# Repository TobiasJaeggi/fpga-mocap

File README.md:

# FPGA-based low-cost motion capture
Infrared-based motion capture.
Image processing is done the [GECKO5Modular](https://github.com/logisim-evolution/GECKO5Education) (formerly GECKO5Education V2.0), an educational FPGA platform.
I created this system as part of masters degree in electrical engineering at Bern University of Applied Sciences (BFH).

> [!NOTE]
> Solving marker correspondence using epipolar geometry is not yet implemented.
> As a result, the Python software is currently only able to track a single marker.

# Blob Detector
Marker detection unit hosting FGPA, microcontroller, IR camera, IR LEDs and PoE module.

# Demo
The system tracking a reflective marker.

[demo video](https://youtu.be/6Va6dF9vp88)

# Mechanical design
[onshape project](https://cad.onshape.com/documents/1d5331a2d4403797078fc34d/w/9683c0b739c4abd1173768d9/e/775ed87ad6031a9883c39a66?renderMode=0&uiState=687d36ef6178f96628e9789b)

# Documentation
`doc/Low-Cost_Motion_Capture.pdf`

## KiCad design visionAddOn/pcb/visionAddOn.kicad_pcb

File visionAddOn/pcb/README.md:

# `visionAddOn/hardware`
An addon for the [GECKO5Education](https://github.com/logisim-evolution/GECKO5Education) intended for IR based MoCap featuring
- STM32F767 with external RAM, EEPROM and external Watchdog
- Power Over Ethernet
- Connector for [KLT-E4MPF-OV9281 V4.2 NIR Camera](http://modulecamera.com)
- switchable 5V supply for external IR stroble LED
# known issues
## V1.0
### nINT/REFCLK0 does not output a clock
Pin 2 (LED2/nINIT/nPME/nINTSEL) on LAN87 needs a pulldown. Also, remove pulldown on LED1/nINT/nPME/REGOFF.
 
# Attribution
## Project Template
This project is based on the GECKO5 [addonTemplate](https://github.com/logisim-evolution/GECKO5Education/tree/main/kicad/addonTemplate)

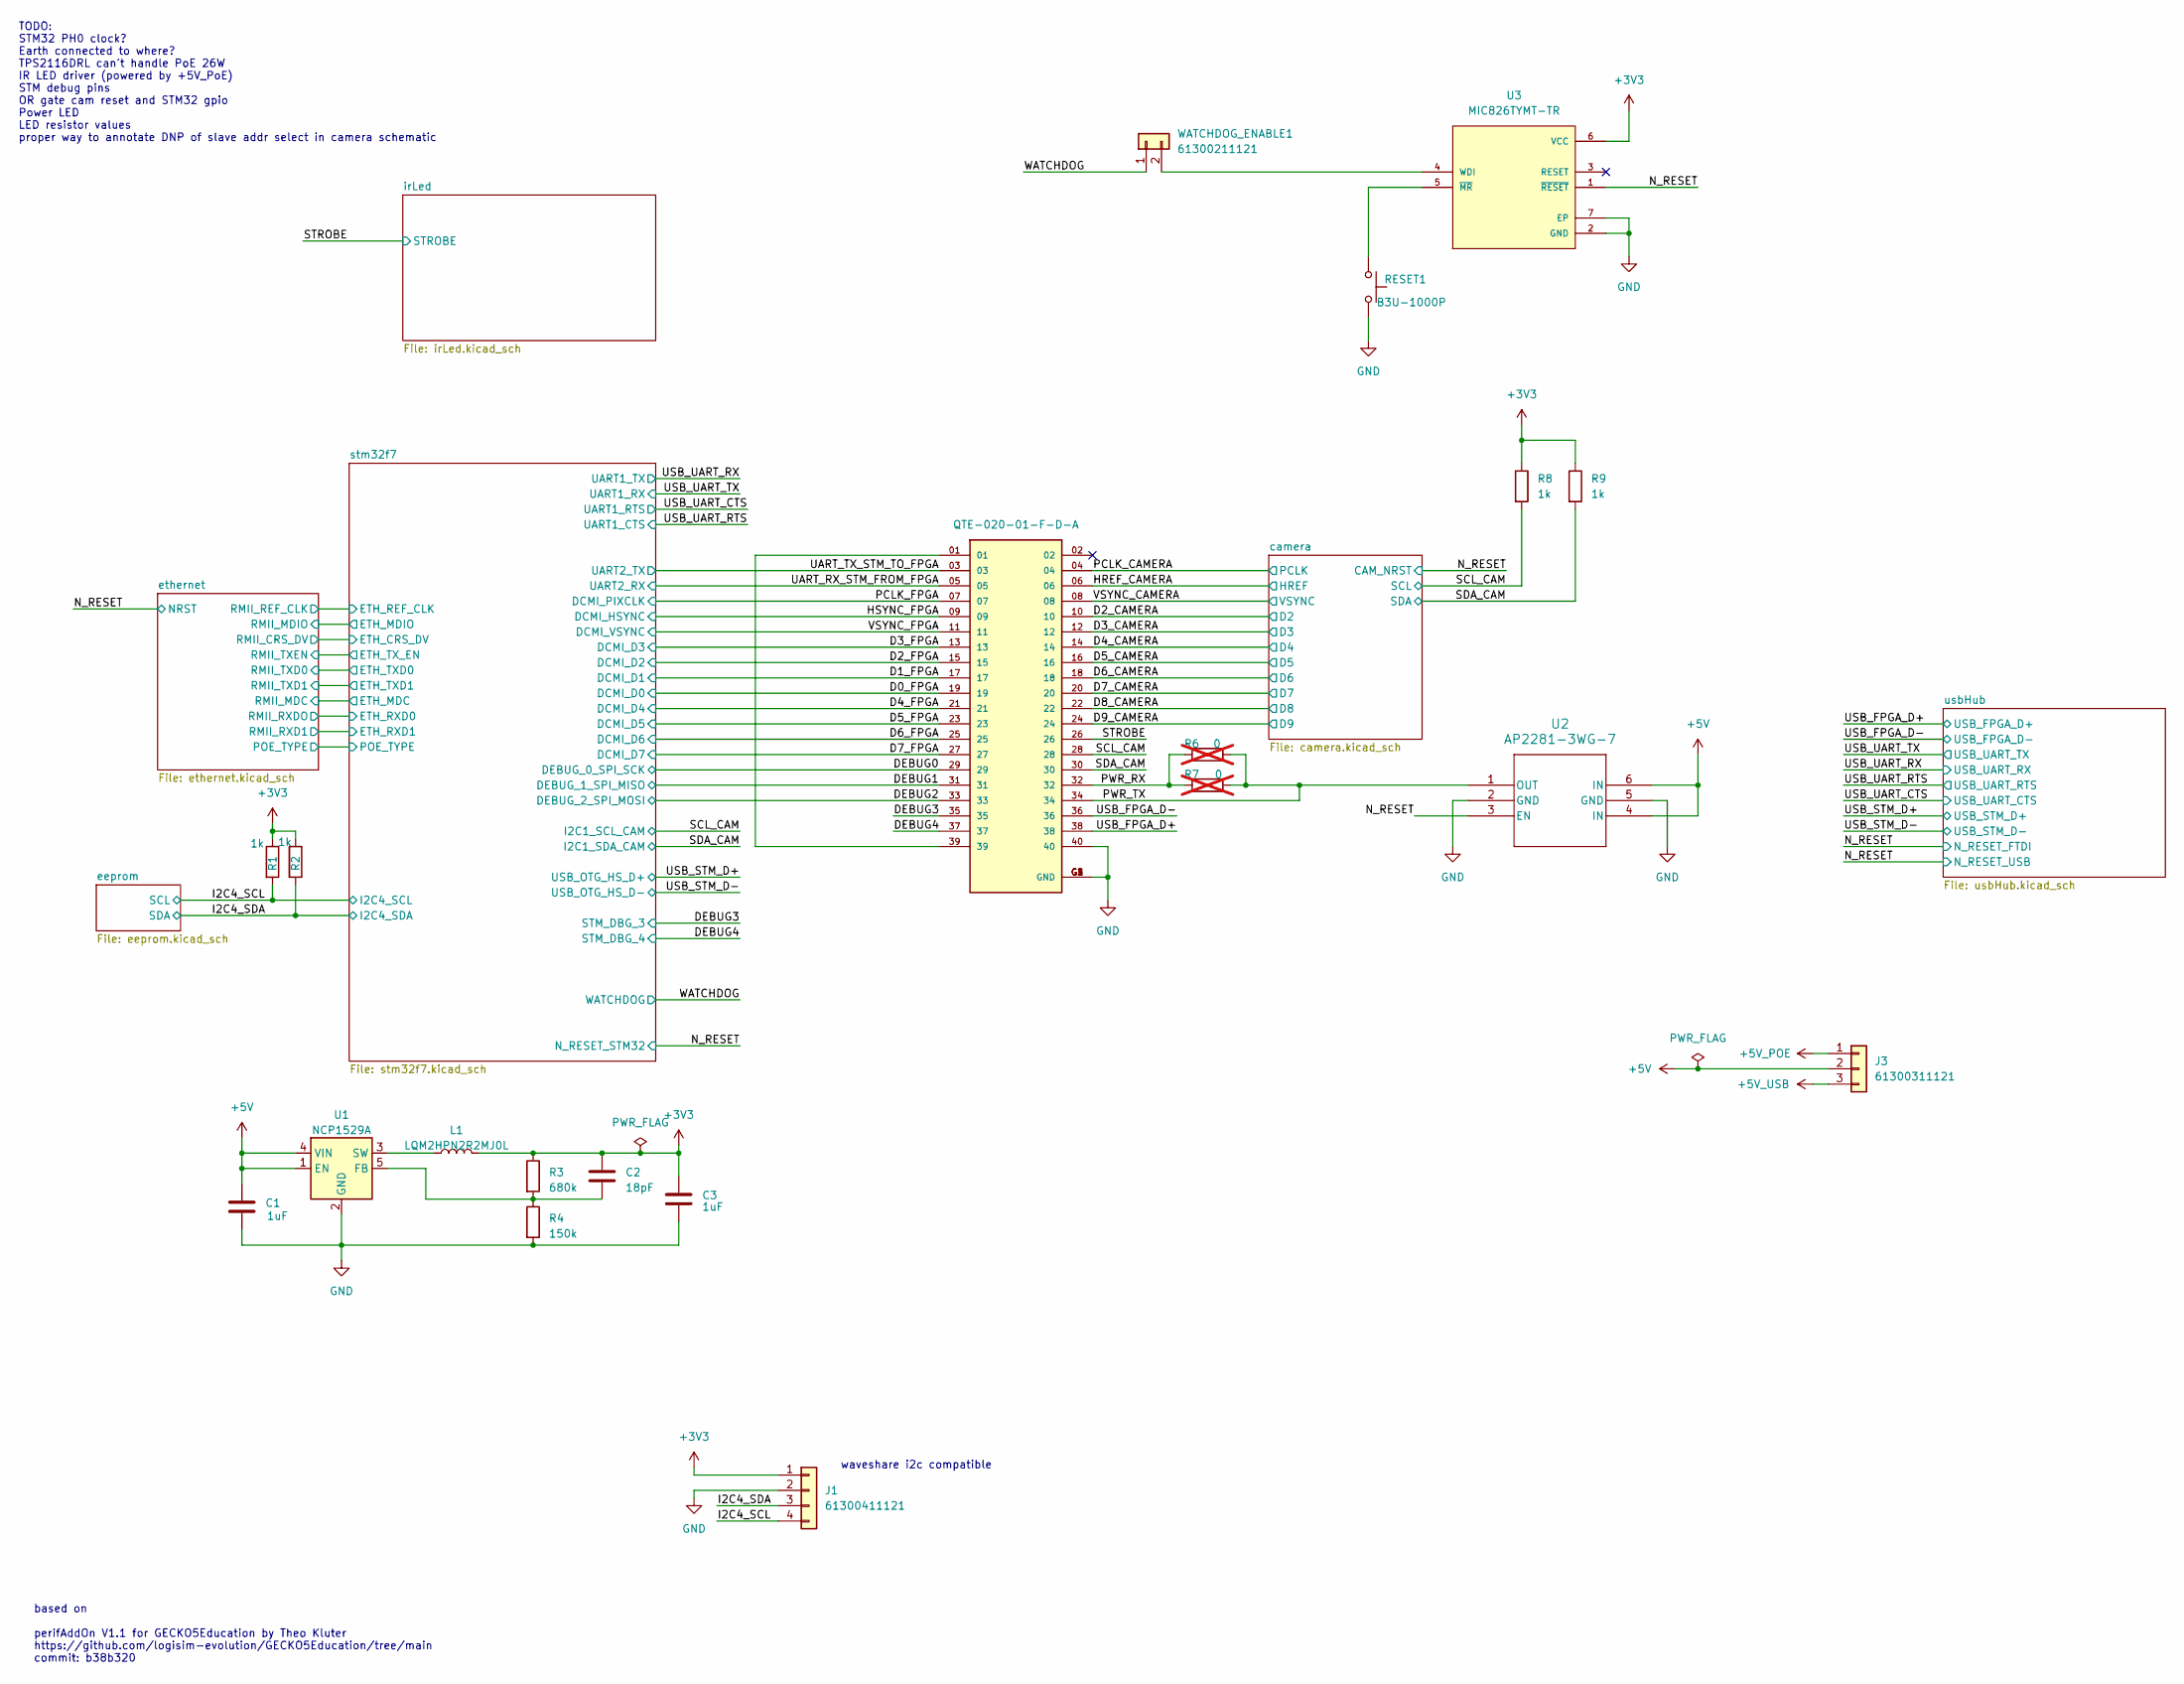
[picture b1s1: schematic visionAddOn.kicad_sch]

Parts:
C1, C3: 1uF; C_0603_1608Metric; DigiKey-Partnumber 445-4112-2-ND
C2: 18pF; C_0402_1005Metric; DigiKey-Partnumber 490-8082-2-ND
J1: 61300411121; PinHeader_1x04_P2.54mm_Vertical; DigiKey-Partnumber 732-5317-ND
J2: QTE-020-01-F-D-A; SAMTEC_QTE-020-01-X-D-A; DigiKey-Partnumber 612-QTE-020-01-F-D-A-TR-ND
J3: 61300311121; PinHeader_1x03_P2.54mm_Vertical; DigiKey-Partnumber 732-5316-ND
L1: LQM2HPN2R2MJ0L; DigiKey-Partnumber 490-6700-2-ND
R1, R2, R8, R9: 1k; R_0402_1005Metric; DigiKey-Partnumber 311-1.0KJRTR-ND
R3: 680k; R_0402_1005Metric; DigiKey-Partnumber 311-680KJRTR-ND
R4: 150k; R_0402_1005Metric; DigiKey-Partnumber 311-150KLRTR-ND
R6, R7: 0; R_0402_1005Metric; DigiKey-Partnumber 311-0.0JRTR-ND; not fitted
RESET1: B3U-1000P; SW_B3U-1000P_OMR; DigiKey-Partnumber SW1020TR-ND
U1: NCP1529A; SOT-23-5; DigiKey-Partnumber NCP1529ASNT1GOSTR-ND
U2: AP2281-3WG-7; SOT26_DIO; DigiKey-Partnumber AP2281-3WG-7DITR-ND
U3: MIC826TYMT-TR; MIC826TYMT-TR_SON50P160X160X60-7N; DigiKey-Partnumber 576-4375-2-ND
WATCHDOG_ENABLE1: 61300211121; PinHeader_1x02_P2.54mm_Vertical; DigiKey-Partnumber 732-5315-ND

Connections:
+3V3: C2.1, C3.1, J1.1, L1.2, R1.1, R2.1, R3.1, R8.1, R9.1, U3.6 (VCC); also elsewhere on the board
+5V: C1.1, J3.2, U1.1 (EN), U1.4 (VIN), U2.4 (IN), U2.6 (IN)
+5V_POE: J3.1; also elsewhere on the board
+5V_USB: J3.3; also elsewhere on the board
/D0_FPGA: J2.19; also elsewhere on the board
/D1_FPGA: J2.17; also elsewhere on the board
/D2_CAMERA: J2.10; also elsewhere on the board
/D2_FPGA: J2.15; also elsewhere on the board
/D3_CAMERA: J2.12; also elsewhere on the board
/D3_FPGA: J2.13; also elsewhere on the board
/D4_CAMERA: J2.14; also elsewhere on the board
/D4_FPGA: J2.21; also elsewhere on the board
/D5_CAMERA: J2.16; also elsewhere on the board
/D5_FPGA: J2.23; also elsewhere on the board
/D6_CAMERA: J2.18; also elsewhere on the board
/D6_FPGA: J2.25; also elsewhere on the board
/D7_CAMERA: J2.20; also elsewhere on the board
/D7_FPGA: J2.27; also elsewhere on the board
/D8_CAMERA: J2.22; also elsewhere on the board
/D9_CAMERA: J2.24; also elsewhere on the board
/DEBUG0: J2.29; also elsewhere on the board
/DEBUG1: J2.31; also elsewhere on the board
/DEBUG2: J2.33; also elsewhere on the board
/DEBUG3: J2.35; also elsewhere on the board
/DEBUG4: J2.37; also elsewhere on the board
/HREF_CAMERA: J2.06; also elsewhere on the board
/HSYNC_FPGA: J2.09; also elsewhere on the board
/I2C4_SCL: J1.4, R1.2; also elsewhere on the board
/I2C4_SDA: J1.3, R2.2; also elsewhere on the board
/N_RESET: U2.3 (EN), U3.1 (~RESET); also elsewhere on the board
/PCLK_CAMERA: J2.04; also elsewhere on the board
/PCLK_FPGA: J2.07; also elsewhere on the board
/PWR_RX: J2.32, R6.1, R7.1
/PWR_TX: J2.34, R6.2, R7.2, U2.1 (OUT)
/SCL_CAM: J2.28, R8.2; also elsewhere on the board
/SDA_CAM: J2.30, R9.2; also elsewhere on the board
/STROBE: J2.26; also elsewhere on the board
/UART_RX_STM_FROM_FPGA: J2.05; also elsewhere on the board
/UART_TX_STM_TO_FPGA: J2.03; also elsewhere on the board
/USB_FPGA_D+: J2.38; also elsewhere on the board
/USB_FPGA_D-: J2.36; also elsewhere on the board
/VSYNC_CAMERA: J2.08; also elsewhere on the board
/VSYNC_FPGA: J2.11; also elsewhere on the board
/WATCHDOG: WATCHDOG_ENABLE1.1; also elsewhere on the board
GND: C1.2, C3.2, J1.2, J2.40, J2.G1 (GND), J2.G2 (GND), J2.G3 (GND), J2.G4 (GND), R4.2, RESET1.2, U1.2 (GND), U2.2 (GND), U2.5 (GND), U3.2 (GND), U3.7 (EP); also elsewhere on the board
unnamed: J2.01, J2.39
unnamed: C2.2, R3.2, R4.1, U1.5 (FB)
unnamed: L1.1, U1.3 (SW)
unnamed: U3.4 (WDI), WATCHDOG_ENABLE1.2
unnamed: RESET1.1, U3.5 (~MR)

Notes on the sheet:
waveshare i2c compatible
TODO: STM32 PH0 clock? Earth connected to where? TPS2116DRL can't handle PoE 26W IR LED driver (powered by +5V_PoE) STM debug pins OR gate cam reset and STM32 gpio Power LED LED resistor values proper way to annotate DNP of slave addr select in camera schematic
based on perifAddOn V1.1 for GECKO5Education by Theo Kluter https://github.com/logisim-evolution/GECKO5Education/tree/main commit: b38b320

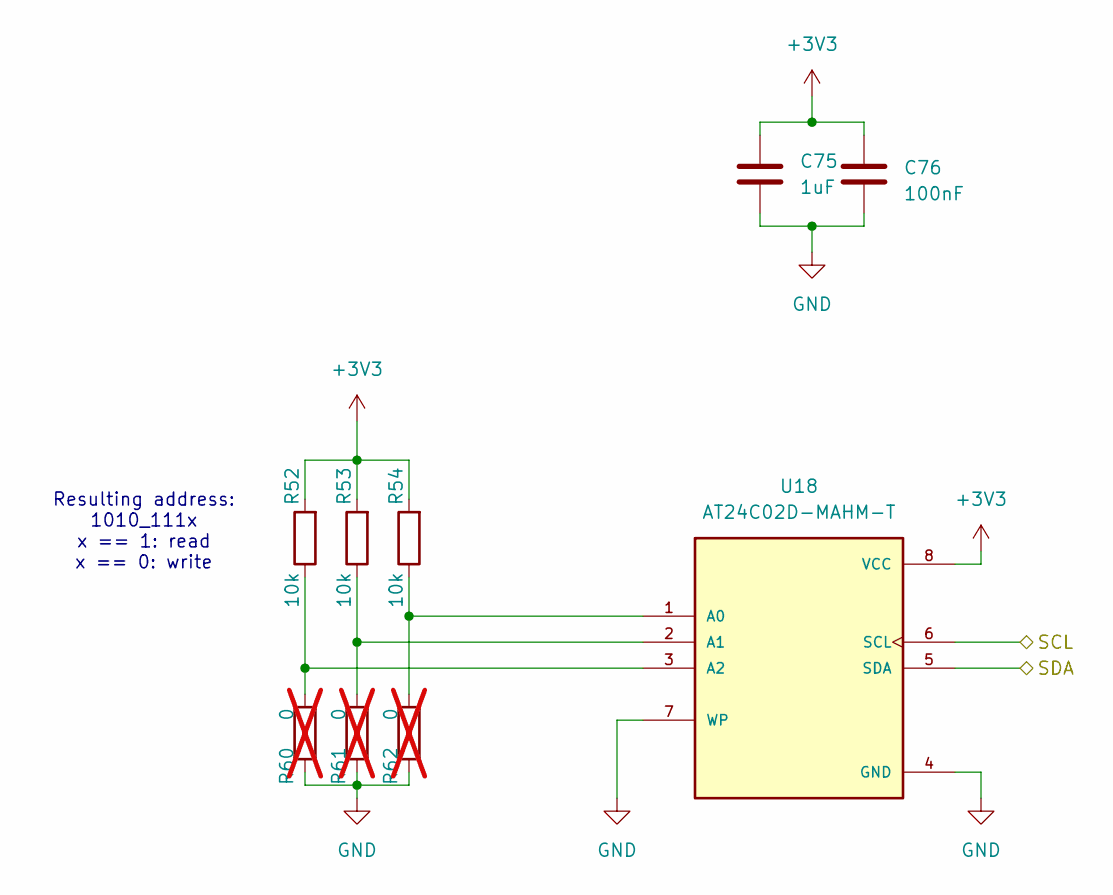
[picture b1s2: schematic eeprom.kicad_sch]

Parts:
C75: 1uF; C_0402_1005Metric; DigiKey-Partnumber 490-10024-2-ND
C76: 100nF; C_0402_1005Metric; DigiKey-Partnumber 490-6328-2-ND
R52, R53, R54: 10k; R_0402_1005Metric; DigiKey-Partnumber 311-10KJRTR-ND
R60, R61, R62: 0; R_0402_1005Metric; DigiKey-Partnumber 311-0.0JRTR-ND; not fitted
U18: AT24C02D-MAHM-T; AT24C02D-MAHM-T_SON50P200X300X60-9N; DigiKey-Partnumber AT24C02D-MAHM-TTR-ND

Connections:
+3V3: C75.1, C76.1, R52.2, R53.2, R54.2, U18.8 (VCC); also elsewhere on the board
/I2C4_SCL: U18.6 (SCL); also elsewhere on the board
/I2C4_SDA: U18.5 (SDA); also elsewhere on the board
GND: C75.2, C76.2, R60.1, R61.1, R62.1, U18.4 (GND), U18.7 (WP); also elsewhere on the board
unnamed: R54.1, R62.2, U18.1 (A0)
unnamed: R53.1, R61.2, U18.2 (A1)
unnamed: R52.1, R60.2, U18.3 (A2)

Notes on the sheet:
Resulting address: 1010_111x x == 1: read x == 0: write

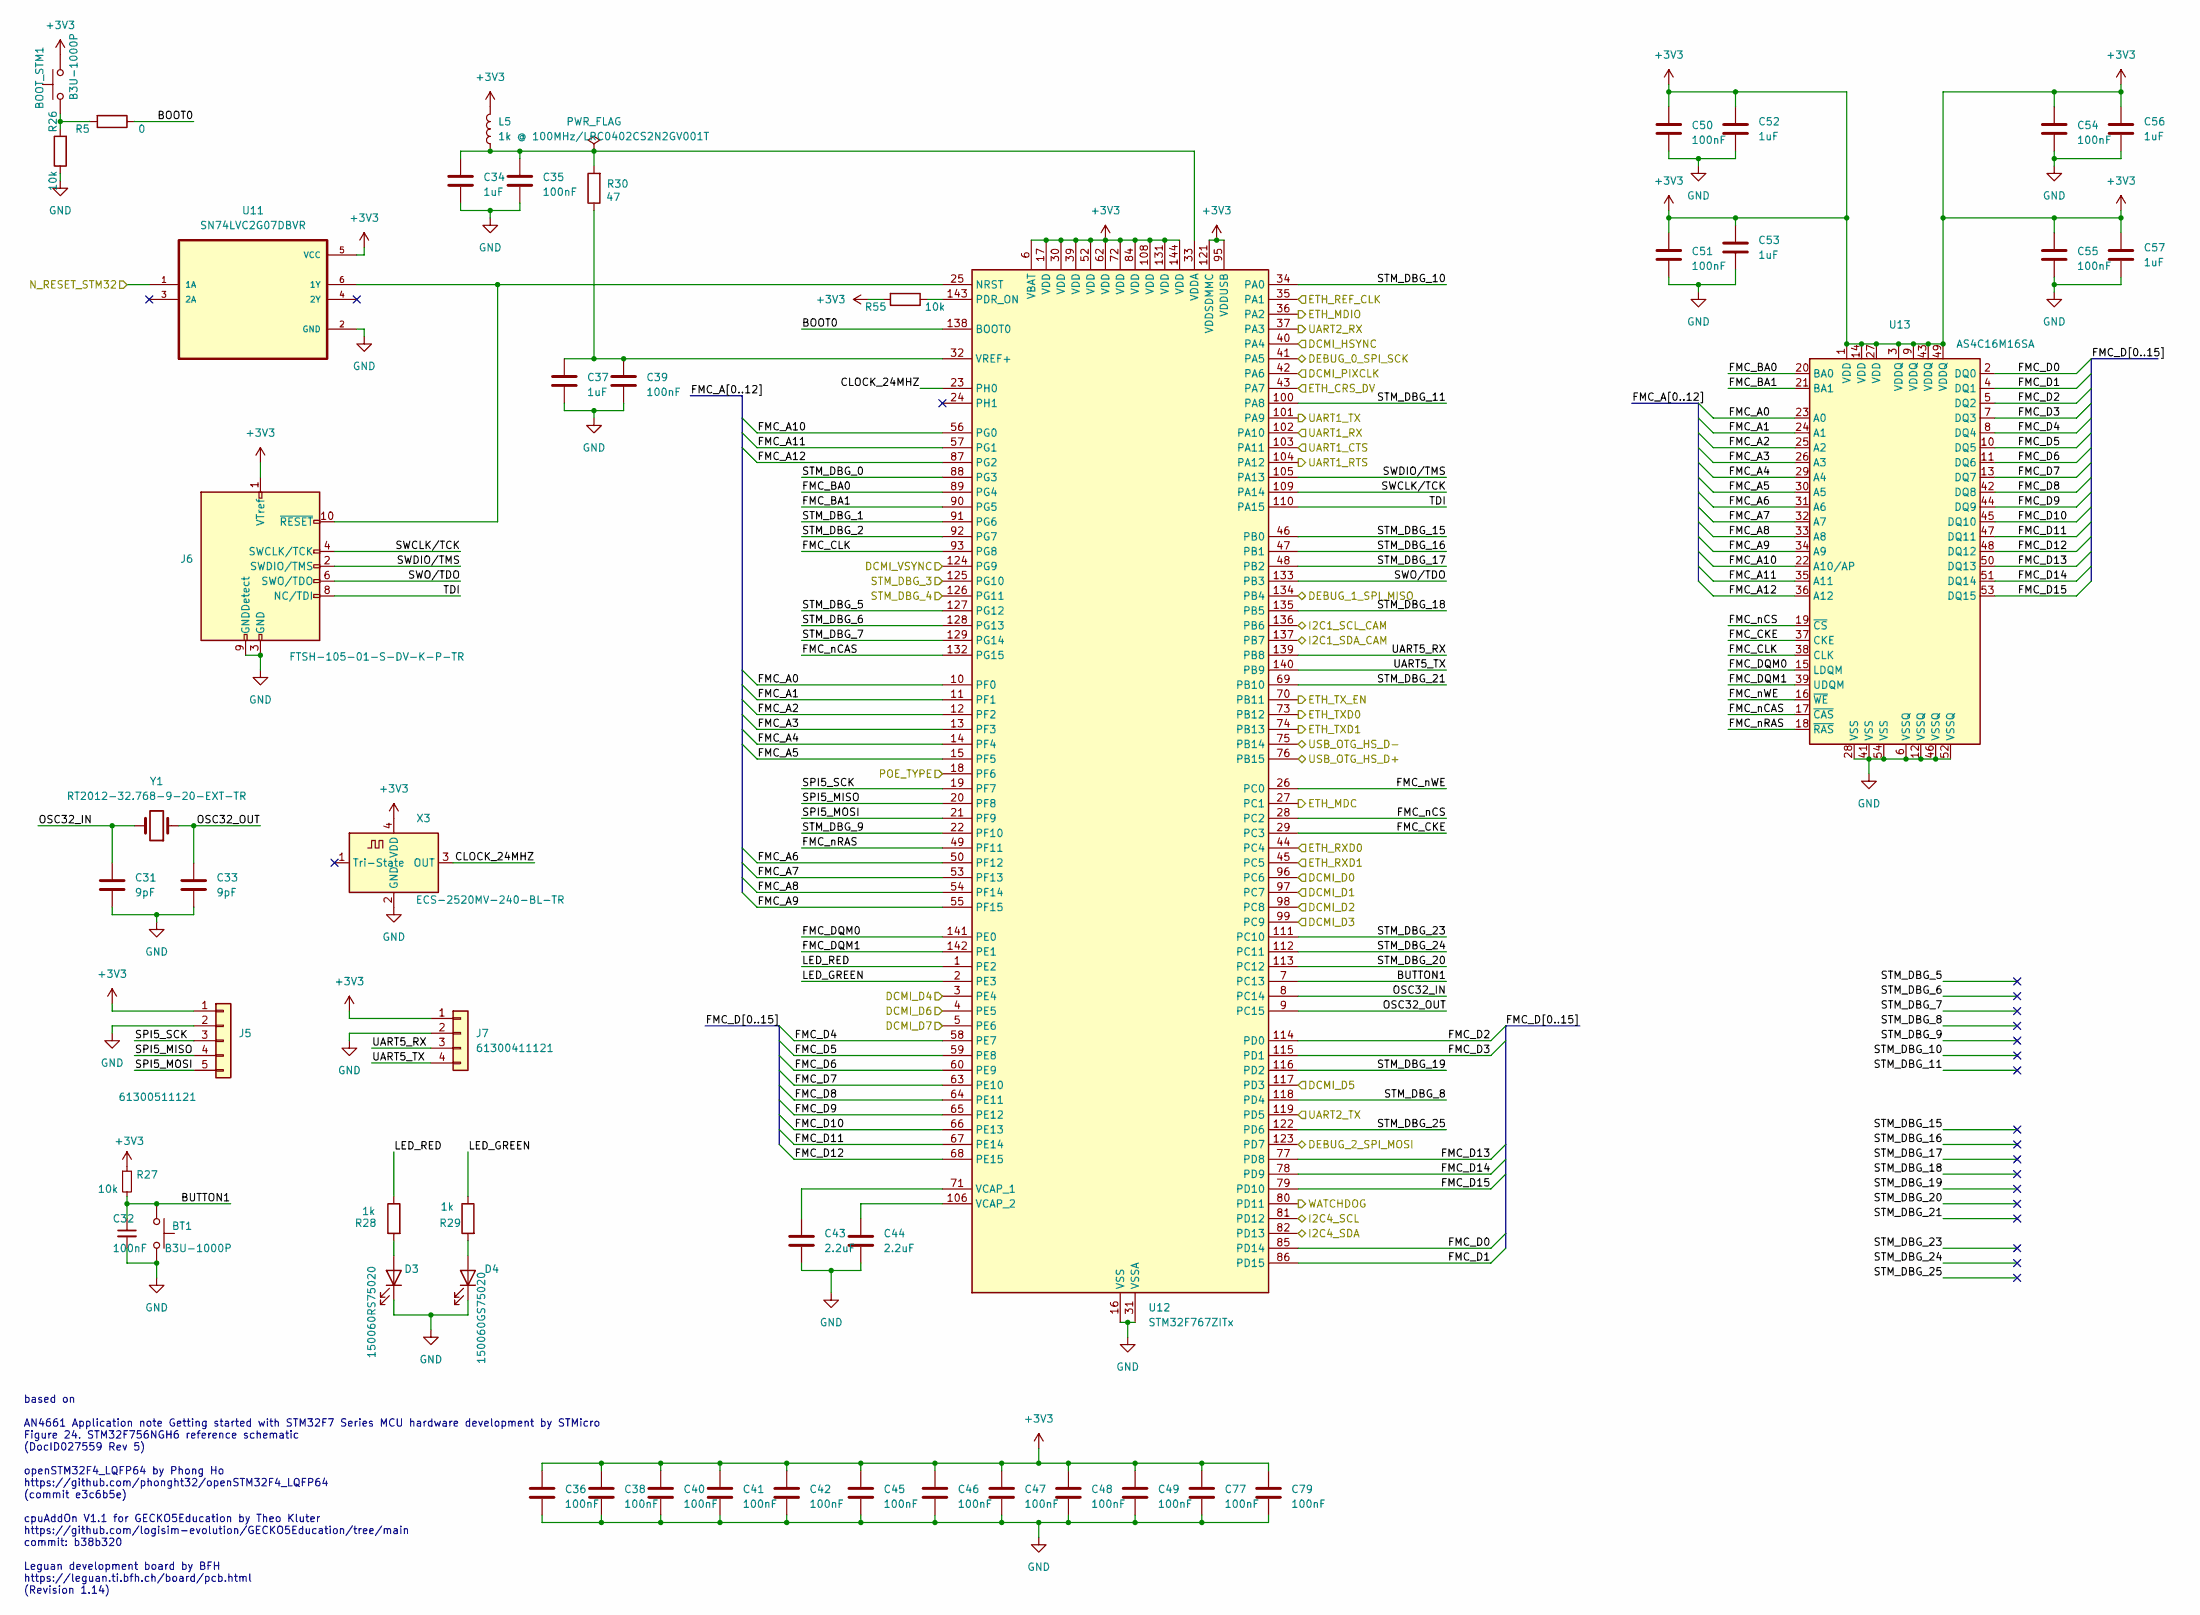
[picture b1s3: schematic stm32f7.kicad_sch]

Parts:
BOOT_STM1: B3U-1000P; SW_B3U-1000P_OMR; DigiKey-Partnumber SW1020TR-ND
BT1: B3U-1000P; SW_B3U-1000P_OMR; DigiKey-Partnumber SW1020TR-ND
C31, C33: 9pF; C_0402_1005Metric; DigiKey-Partnumber 490-8232-2-ND
C32, C35, C36, C38, C39, C40, C41, C42, C45, C46, C47, C48, C49, C50, C51, C54, C55, C77, C79: 100nF; C_0402_1005Metric; DigiKey-Partnumber 490-6328-2-ND
C34, C37, C52, C53, C56, C57: 1uF; C_0402_1005Metric; DigiKey-Partnumber 490-10024-2-ND
C43, C44: 2.2uF; C_0402_1005Metric; DigiKey-Partnumber 490-10012-2-ND
D3: 150060RS75020; LED_0603_1608Metric; DigiKey-Partnumber 732-150060RS75020TR-ND
D4: 150060GS75020; LED_0603_1608Metric; DigiKey-Partnumber 732-150060GS75020TR-ND
J5: 61300511121; PinHeader_1x05_P2.54mm_Vertical; DigiKey-Partnumber 732-5318-ND
J6: FTSH-105-01-S-DV-K-P-TR; SAMTEC_FTSH-105-01-S-DV-TR; DigiKey-Partnumber SAM13935TR-ND
J7: 61300411121; PinHeader_1x04_P2.54mm_Vertical; DigiKey-Partnumber 732-5317-ND
L5: 1k @ 100MHz/LRC0402CS2N2GV001T; L_0402_1005Metric; DigiKey-Partnumber 712-LRC0402CS2N2GV001TTR-ND
R5: 0; R_0402_1005Metric; DigiKey-Partnumber 311-0.0JRTR-ND
R26, R27, R55: 10k; R_0402_1005Metric; DigiKey-Partnumber 311-10KJRTR-ND
R28, R29: 1k; R_0402_1005Metric; DigiKey-Partnumber 311-1.0KJRTR-ND
R30: 47; R_0402_1005Metric; DigiKey-Partnumber RMCF0402JT47R0TR-ND
U11: SN74LVC2G07DBVR; SOT95P280X145-6N; DigiKey-Partnumber 296-13494-2-ND
U12: STM32F767ZITx; LQFP-144_20x20mm_P0.5mm; DigiKey-Partnumber 497-16521-ND
U13: AS4C16M16SA; TSOP-II-54_22.2x10.16mm_P0.8mm; DigiKey-Partnumber 1450-1252-ND
X3: ECS-2520MV-240-BL-TR; Oscillator_SMD_ECS_2520MV-xxx-xx-4Pin_2.5x2.0mm; DigiKey-Partnumber 50-ECS-2520MV-240-BL-TR-ND
Y1: RT2012-32.768-9-20-EXT-TR; Crystal_SMD_2012-2Pin_2.0x1.2mm; DigiKey-Partnumber 2151-RT2012-32.768-9-20-EXT-TR-ND

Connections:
+3V3: BOOT_STM1.2, C36.1, C38.1, C40.1, C41.1, C42.1, C45.1, C46.1, C47.1, C48.1, C49.1, C50.1, C51.1, C52.1, C53.1, C54.1, C55.1, C56.1, C57.1, C77.1, C79.1, J5.1, J6.1 (VTref), J7.1, L5.2, R27.1, R55.2, U11.5 (VCC), U12.6 (VBAT), U12.17 (VDD), U12.30 (VDD), U12.39 (VDD), U12.52 (VDD), U12.62 (VDD), U12.72 (VDD), U12.84 (VDD), U12.95 (VDDUSB), U12.108 (VDD), U12.121 (VDDSDMMC), U12.131 (VDD), U12.144 (VDD), U13.1 (VDD), U13.3 (VDDQ), U13.9 (VDDQ), U13.14 (VDD), U13.27 (VDD), U13.43 (VDDQ), U13.49 (VDDQ), X3.4 (VDD); also elsewhere on the board
/D0_FPGA: U12.96 (PC6); also elsewhere on the board
/D1_FPGA: U12.97 (PC7); also elsewhere on the board
/D2_FPGA: U12.98 (PC8); also elsewhere on the board
/D3_FPGA: U12.99 (PC9); also elsewhere on the board
/D4_FPGA: U12.3 (PE4); also elsewhere on the board
/D5_FPGA: U12.117 (PD3); also elsewhere on the board
/D6_FPGA: U12.4 (PE5); also elsewhere on the board
/D7_FPGA: U12.5 (PE6); also elsewhere on the board
/DEBUG0: U12.41 (PA5); also elsewhere on the board
/DEBUG1: U12.134 (PB4); also elsewhere on the board
/DEBUG2: U12.123 (PD7); also elsewhere on the board
/DEBUG3: U12.125 (PG10); also elsewhere on the board
/DEBUG4: U12.126 (PG11); also elsewhere on the board
/HSYNC_FPGA: U12.40 (PA4); also elsewhere on the board
/I2C4_SCL: U12.81 (PD12); also elsewhere on the board
/I2C4_SDA: U12.82 (PD13); also elsewhere on the board
/N_RESET: U11.1 (1A); also elsewhere on the board
/PCLK_FPGA: U12.42 (PA6); also elsewhere on the board
/SCL_CAM: U12.136 (PB6); also elsewhere on the board
/SDA_CAM: U12.137 (PB7); also elsewhere on the board
/UART_RX_STM_FROM_FPGA: U12.37 (PA3); also elsewhere on the board
/UART_TX_STM_TO_FPGA: U12.119 (PD5); also elsewhere on the board
/USB_STM_D+: U12.76 (PB15); also elsewhere on the board
/USB_STM_D-: U12.75 (PB14); also elsewhere on the board
/USB_UART_CTS: U12.104 (PA12); also elsewhere on the board
/USB_UART_RTS: U12.103 (PA11); also elsewhere on the board
/USB_UART_RX: U12.101 (PA9); also elsewhere on the board
/USB_UART_TX: U12.102 (PA10); also elsewhere on the board
/VSYNC_FPGA: U12.124 (PG9); also elsewhere on the board
/WATCHDOG: U12.80 (PD11); also elsewhere on the board
/ethernet/POE_TYPE: U12.18 (PF6); also elsewhere on the board
/ethernet/RMII_CRS_DV: U12.43 (PA7); also elsewhere on the board
/ethernet/RMII_MDC: U12.27 (PC1); also elsewhere on the board
/ethernet/RMII_MDIO: U12.36 (PA2); also elsewhere on the board
/ethernet/RMII_REF_CLK: U12.35 (PA1); also elsewhere on the board
/ethernet/RMII_RXD1: U12.45 (PC5); also elsewhere on the board
/ethernet/RMII_RXDO: U12.44 (PC4); also elsewhere on the board
/ethernet/RMII_TXD0: U12.73 (PB12); also elsewhere on the board
/ethernet/RMII_TXD1: U12.74 (PB13); also elsewhere on the board
/ethernet/RMII_TXEN: U12.70 (PB11); also elsewhere on the board
/stm32f7/BOOT0: R5.1, U12.138 (BOOT0)
/stm32f7/BUTTON1: BT1.1, C32.1, R27.2, U12.7 (PC13)
/stm32f7/CLOCK_24MHZ: U12.23 (PH0), X3.3 (OUT)
/stm32f7/FMC_A0: U12.10 (PF0), U13.23 (A0)
/stm32f7/FMC_A1: U12.11 (PF1), U13.24 (A1)
/stm32f7/FMC_A2: U12.12 (PF2), U13.25 (A2)
/stm32f7/FMC_A3: U12.13 (PF3), U13.26 (A3)
/stm32f7/FMC_A4: U12.14 (PF4), U13.29 (A4)
/stm32f7/FMC_A5: U12.15 (PF5), U13.30 (A5)
/stm32f7/FMC_A6: U12.50 (PF12), U13.31 (A6)
/stm32f7/FMC_A7: U12.53 (PF13), U13.32 (A7)
/stm32f7/FMC_A8: U12.54 (PF14), U13.33 (A8)
/stm32f7/FMC_A9: U12.55 (PF15), U13.34 (A9)
/stm32f7/FMC_A10: U12.56 (PG0), U13.22 (A10/AP)
/stm32f7/FMC_A11: U12.57 (PG1), U13.35 (A11)
/stm32f7/FMC_A12: U12.87 (PG2), U13.36 (A12)
/stm32f7/FMC_BA0: U12.89 (PG4), U13.20 (BA0)
/stm32f7/FMC_BA1: U12.90 (PG5), U13.21 (BA1)
/stm32f7/FMC_CKE: U12.29 (PC3), U13.37 (CKE)
/stm32f7/FMC_CLK: U12.93 (PG8), U13.38 (CLK)
/stm32f7/FMC_D0: U12.85 (PD14), U13.2 (DQ0)
/stm32f7/FMC_D1: U12.86 (PD15), U13.4 (DQ1)
/stm32f7/FMC_D2: U12.114 (PD0), U13.5 (DQ2)
/stm32f7/FMC_D3: U12.115 (PD1), U13.7 (DQ3)
/stm32f7/FMC_D4: U12.58 (PE7), U13.8 (DQ4)
/stm32f7/FMC_D5: U12.59 (PE8), U13.10 (DQ5)
/stm32f7/FMC_D6: U12.60 (PE9), U13.11 (DQ6)
/stm32f7/FMC_D7: U12.63 (PE10), U13.13 (DQ7)
/stm32f7/FMC_D8: U12.64 (PE11), U13.42 (DQ8)
/stm32f7/FMC_D9: U12.65 (PE12), U13.44 (DQ9)
/stm32f7/FMC_D10: U12.66 (PE13), U13.45 (DQ10)
/stm32f7/FMC_D11: U12.67 (PE14), U13.47 (DQ11)
/stm32f7/FMC_D12: U12.68 (PE15), U13.48 (DQ12)
/stm32f7/FMC_D13: U12.77 (PD8), U13.50 (DQ13)
/stm32f7/FMC_D14: U12.78 (PD9), U13.51 (DQ14)
/stm32f7/FMC_D15: U12.79 (PD10), U13.53 (DQ15)
/stm32f7/FMC_DQM0: U12.141 (PE0), U13.15 (LDQM)
/stm32f7/FMC_DQM1: U12.142 (PE1), U13.39 (UDQM)
/stm32f7/FMC_nCAS: U12.132 (PG15), U13.17 (~CAS)
/stm32f7/FMC_nCS: U12.28 (PC2), U13.19 (~CS)
/stm32f7/FMC_nRAS: U12.49 (PF11), U13.18 (~RAS)
/stm32f7/FMC_nWE: U12.26 (PC0), U13.16 (~WE)
/stm32f7/LED_GREEN: R29.1, U12.2 (PE3)
/stm32f7/LED_RED: R28.1, U12.1 (PE2)
/stm32f7/OSC32_IN: C31.1, U12.8 (PC14), Y1.2
/stm32f7/OSC32_OUT: C33.1, U12.9 (PC15), Y1.1
/stm32f7/SPI5_MISO: J5.4, U12.20 (PF8)
/stm32f7/SPI5_MOSI: J5.5, U12.21 (PF9)
/stm32f7/SPI5_SCK: J5.3, U12.19 (PF7)
/stm32f7/STM_DBG_0: U12.88 (PG3)
/stm32f7/STM_DBG_1: U12.91 (PG6)
/stm32f7/STM_DBG_2: U12.92 (PG7)
/stm32f7/STM_DBG_5: U12.127 (PG12)
/stm32f7/STM_DBG_6: U12.128 (PG13)
/stm32f7/STM_DBG_7: U12.129 (PG14)
/stm32f7/STM_DBG_8: U12.118 (PD4)
/stm32f7/STM_DBG_9: U12.22 (PF10)
/stm32f7/STM_DBG_10: U12.34 (PA0)
/stm32f7/STM_DBG_11: U12.100 (PA8)
/stm32f7/STM_DBG_15: U12.46 (PB0)
/stm32f7/STM_DBG_16: U12.47 (PB1)
/stm32f7/STM_DBG_17: U12.48 (PB2)
/stm32f7/STM_DBG_18: U12.135 (PB5)
/stm32f7/STM_DBG_19: U12.116 (PD2)
/stm32f7/STM_DBG_20: U12.113 (PC12)
/stm32f7/STM_DBG_21: U12.69 (PB10)
/stm32f7/STM_DBG_23: U12.111 (PC10)
/stm32f7/STM_DBG_24: U12.112 (PC11)
/stm32f7/STM_DBG_25: U12.122 (PD6)
/stm32f7/SWCLK/TCK: J6.4 (SWCLK/TCK), U12.109 (PA14)
/stm32f7/SWDIO/TMS: J6.2 (SWDIO/TMS), U12.105 (PA13)
/stm32f7/SWO/TDO: J6.6 (SWO/TDO), U12.133 (PB3)
/stm32f7/TDI: J6.8 (NC/TDI), U12.110 (PA15)
/stm32f7/UART5_RX: J7.3, U12.139 (PB8)
/stm32f7/UART5_TX: J7.4, U12.140 (PB9)
GND: BT1.2, C31.2, C32.2, C33.2, C34.2, C35.2, C36.2, C37.2, C38.2, C39.2, C40.2, C41.2, C42.2, C43.2, C44.2, C45.2, C46.2, C47.2, C48.2, C49.2, C50.2, C51.2, C52.2, C53.2, C54.2, C55.2, C56.2, C57.2, C77.2, C79.2, D3.1 (K), D4.1 (K), J5.2, J6.3 (GND), J6.5 (GND), J6.9 (GNDDetect), J7.2, R26.1, U11.2 (GND), U12.16 (VSS), U12.31 (VSSA), U12.38 (VSS), U12.51 (VSS), U12.61 (VSS), U12.83 (VSS), U12.94 (VSS), U12.107 (VSS), U12.120 (VSS), U12.130 (VSS), U13.6 (VSSQ), U13.12 (VSSQ), U13.28 (VSS), U13.41 (VSS), U13.46 (VSSQ), U13.52 (VSSQ), U13.54 (VSS), X3.2 (GND); also elsewhere on the board
unnamed: BOOT_STM1.1, R5.2, R26.2
unnamed: D3.2 (A), R28.2
unnamed: D4.2 (A), R29.2
unnamed: J6.10 (~RESET), U11.6 (1Y), U12.25 (NRST)
unnamed: R55.1, U12.143 (PDR_ON)
unnamed: C43.1, U12.71 (VCAP_1)
unnamed: C44.1, U12.106 (VCAP_2)
unnamed: C34.1, C35.1, L5.1, R30.2, U12.33 (VDDA)
unnamed: C37.1, C39.1, R30.1, U12.32 (VREF+)

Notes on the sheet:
based on AN4661 Application note Getting started with STM32F7 Series MCU hardware development by STMicro Figure 24. STM32F756NGH6 reference schematic (DocID027559 Rev 5) openSTM32F4_LQFP64 by Phong Ho https://github.com/phonght32/openSTM32F4_LQFP64 (commit e3c6b5e) cpuAddOn V1.1 for GECKO5Education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

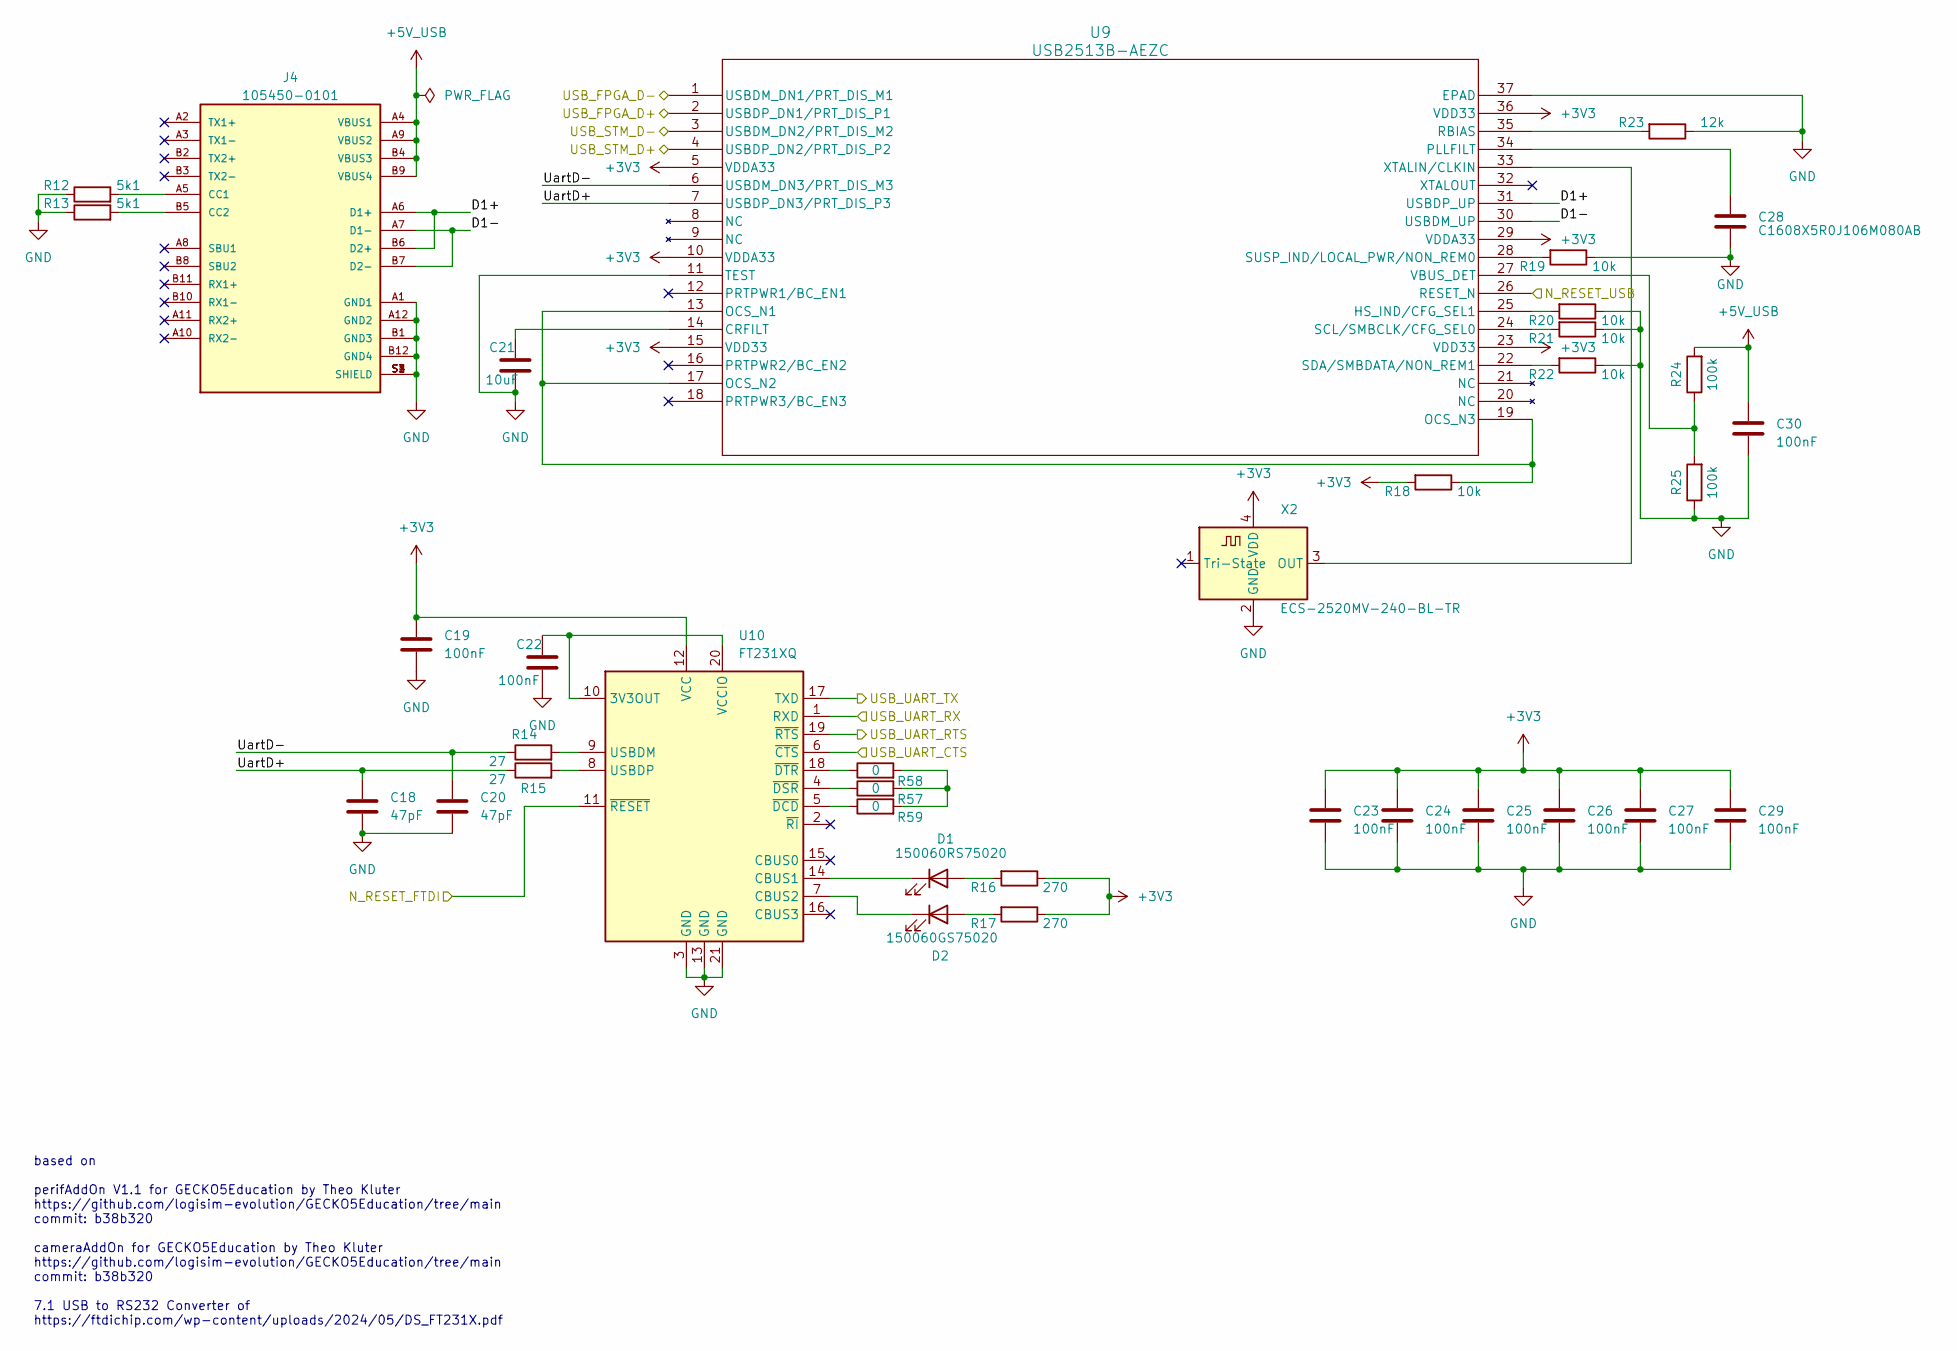
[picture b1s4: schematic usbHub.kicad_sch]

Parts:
C18, C20: 47pF; C_0402_1005Metric; DigiKey-Partnumber 490-5942-2-ND
C19, C22, C23, C24, C25, C26, C27, C29, C30: 100nF; C_0402_1005Metric; DigiKey-Partnumber 490-6328-2-ND
C21: 10uF; C_0603_1608Metric; DigiKey-Partnumber 445-4112-2-ND
C28: C1608X5R0J106M080AB; C_0603_1608Metric; DigiKey-Partnumber 445-4112-2-ND
D1: 150060RS75020; LED_0603_1608Metric; DigiKey-Partnumber 732-150060RS75020TR-ND
D2: 150060GS75020; LED_0603_1608Metric; DigiKey-Partnumber 732-150060GS75020TR-ND
J4: 105450-0101; MOLEX_105450-0101; DigiKey-Partnumber WM12856TR-ND
R12, R13: 5k1; R_0402_1005Metric; DigiKey-Partnumber 311-5.10KLRTR-ND
R14, R15: 27; R_0402_1005Metric; DigiKey-Partnumber P27.0LTR-ND
R16, R17: 270; R_0402_1005Metric; DigiKey-Partnumber 541-4842-2-ND
R18, R19, R20, R21, R22: 10k; R_0402_1005Metric; DigiKey-Partnumber 311-10KJRTR-ND
R23: 12k; R_0402_1005Metric; DigiKey-Partnumber 311-12KJRTR-ND
R24, R25: 100k; R_0402_1005Metric; DigiKey-Partnumber 311-100KLRTR-ND
R57, R58, R59: 0; R_0402_1005Metric; DigiKey-Partnumber 311-0.0JRTR-ND
U9: USB2513B-AEZC; QFN36_6X6MC_MCH; DigiKey-Partnumber USB2513B-AEZC-ND
U10: FT231XQ; QFN-20-1EP_4x4mm_P0.5mm_EP2.5x2.5mm; DigiKey-Partnumber 768-1128-2-ND
X2: ECS-2520MV-240-BL-TR; Oscillator_SMD_ECS_2520MV-xxx-xx-4Pin_2.5x2.0mm; DigiKey-Partnumber 50-ECS-2520MV-240-BL-TR-ND

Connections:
+3V3: C19.1, C23.1, C24.1, C25.1, C26.1, C27.1, C29.1, R16.1, R17.1, R18.2, U9.5 (VDDA33), U9.10 (VDDA33), U9.15 (VDD33), U9.23 (VDD33), U9.29 (VDDA33), U9.36 (VDD33), U10.12 (VCC), X2.4 (VDD); also elsewhere on the board
+5V_USB: C30.1, J4.A4 (VBUS1), J4.A9 (VBUS2), J4.B4 (VBUS3), J4.B9 (VBUS4), R24.2; also elsewhere on the board
/N_RESET: U9.26 (RESET_N), U10.11 (~RESET); also elsewhere on the board
/USB_FPGA_D+: U9.2 (USBDP_DN1/PRT_DIS_P1); also elsewhere on the board
/USB_FPGA_D-: U9.1 (USBDM_DN1/PRT_DIS_M1); also elsewhere on the board
/USB_STM_D+: U9.4 (USBDP_DN2/PRT_DIS_P2); also elsewhere on the board
/USB_STM_D-: U9.3 (USBDM_DN2/PRT_DIS_M2); also elsewhere on the board
/USB_UART_CTS: U10.6 (~CTS); also elsewhere on the board
/USB_UART_RTS: U10.19 (~RTS); also elsewhere on the board
/USB_UART_RX: U10.1 (RXD); also elsewhere on the board
/USB_UART_TX: U10.17 (TXD); also elsewhere on the board
/usbHub/D1+: J4.A6 (D1+), J4.B6 (D2+), U9.31 (USBDP_UP)
/usbHub/D1-: J4.A7 (D1-), J4.B7 (D2-), U9.30 (USBDM_UP)
/usbHub/UartD+: C18.1, R15.1, U9.7 (USBDP_DN3/PRT_DIS_P3)
/usbHub/UartD-: C20.1, R14.1, U9.6 (USBDM_DN3/PRT_DIS_M3)
GND: C18.2, C19.2, C20.2, C21.2, C22.2, C23.2, C24.2, C25.2, C26.2, C27.2, C28.2, C29.2, C30.2, J4.A1 (GND1), J4.A12 (GND2), J4.B1 (GND3), J4.B12 (GND4), J4.S1 (SHIELD), J4.S2 (SHIELD), J4.S3 (SHIELD), J4.S4 (SHIELD), R12.1, R13.1, R19.1, R20.1, R21.1, R22.1, R23.1, R25.1, U9.11 (TEST), U9.37 (EPAD), U10.3 (GND), U10.13 (GND), U10.21 (GND), X2.2 (GND); also elsewhere on the board
unnamed: D1.2 (A), R16.2
unnamed: D1.1 (K), U10.14 (CBUS1)
unnamed: D2.2 (A), R17.2
unnamed: D2.1 (K), U10.7 (CBUS2)
unnamed: J4.A5 (CC1), R12.2
unnamed: J4.B5 (CC2), R13.2
unnamed: R57.2, R58.2, R59.2
unnamed: C21.1, U9.14 (CRFILT)
unnamed: R20.2, U9.25 (HS_IND/CFG_SEL1)
unnamed: R18.1, U9.13 (OCS_N1), U9.17 (OCS_N2), U9.19 (OCS_N3)
unnamed: C28.1, U9.34 (PLLFILT)
unnamed: R23.2, U9.35 (RBIAS)
unnamed: R21.2, U9.24 (SCL/SMBCLK/CFG_SEL0)
unnamed: R22.2, U9.22 (SDA/SMBDATA/NON_REM1)
unnamed: R19.2, U9.28 (SUSP_IND/LOCAL_PWR/NON_REM0)
unnamed: R24.1, R25.2, U9.27 (VBUS_DET)
unnamed: U9.33 (XTALIN/CLKIN), X2.3 (OUT)
unnamed: C22.1, U10.10 (3V3OUT), U10.20 (VCCIO)
unnamed: R14.2, U10.9 (USBDM)
unnamed: R15.2, U10.8 (USBDP)
unnamed: R59.1, U10.5 (~DCD)
unnamed: R57.1, U10.4 (~DSR)
unnamed: R58.1, U10.18 (~DTR)

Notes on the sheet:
based on perifAddOn V1.1 for GECKO5Education by Theo Kluter https://github.com/logisim-evolution/GECKO5Education/tree/main commit: b38b320 cameraAddOn for GECKO5Education by Theo Kluter https://github.com/logisim-evolution/GECKO5Education/tree/main commit: b38b320 7.1 USB to RS232 Converter of http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

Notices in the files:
parts and their libraries:
License: Apache-2.0
